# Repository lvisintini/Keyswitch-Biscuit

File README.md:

# Keyswitch-Biscuit
This is a Kicad project outlining the desing and gerbers for a Keyboard Switch Biscuits

## What is it?

This small PCB fits a single Cherry MX style mechanical keyboard switch and exposes all the connections for easy soldering.

It's designed for those of you interested in making hand-wired custom mechanical keyboards like the [Dactyl Manuform](https://github.com/abstracthat/dactyl-manuform)

There are a bunch of of these around, but this one is different in that:

- It is designed to be used with Kailh hotswap sockets (for solderless removal of keyswitches)
- It has a slot for a [SK6812 MINI-E](https://hackaday.com/2020/01/28/new-part-day-sk6812-mini-e-a-hand-solderable-neopixel-compatible-led/) downward-facing RGB surface mounted LED (you can get a bunch of them [here](https://www.ebay.co.uk/itm/174769617449)
- Allows you to solder the entire key matrix before installing it inside the case. (no need to do this in place)

This design in particular has indentations in each corner so that melted plastic can be used to hold the PCB in place, without the need of glue or screws (though you could still use those if you wanted to)

I designed this when I was preparing to make my own Dactyl Manuform keyboard.

See.. it's layout and shape not flat and it's not possible to buy/make a single board with all the terminals for the key switches you need. This is when this small PCB comes in handy.

You could hand-wire all the key switches together but it would be messy and you would be hard pressed if you wanted to use Kailh hotswap sockets or any kind of RGB features.

## Version and Gerbers
### **v1.0** (gerbers/gerbers-v1.0.zip)

First iteration of the desing.

The RBG footprint used for the SK6812 MINI-E was messed up and the connections did not match.

The board was successfully printed with JLCPCB (as 5x5 panel), the only the Rows and Cols are really usable.

Leaving this hear for the sake of archiving.

### **v1.1** (gerbers/gerbers-v1.1.zip)

This version was the first usable MVP and it was successfully used in my own Dactyl Manuform build.

Works great!

The board was successfully printed with JLCPCB though I dont remember doing much checking tolerances.

I used a 1.6 thickness with a 1oz copper layer and a LeadFree HASL-RoHS finish.

Potentially improvements:
    
 -  Solid Pads instead of THT may allow for easier wiring (though they may require better soldering skills)
 -  The traces themselves could be a bit thicker (not sure if there is enough space)#

## Bonus

mount.stl is 3D-printable part that can be used to firmly hold in place the Keyswitch-Biscuit to allow for easy soldering.
It can come in handy to get a few of these and glue them to a working surface, spaced so that there is equal distances between them.
If you are planning on hand-wiring a large matrix, it may make it easy to solder the wires and keep of a consistent length.

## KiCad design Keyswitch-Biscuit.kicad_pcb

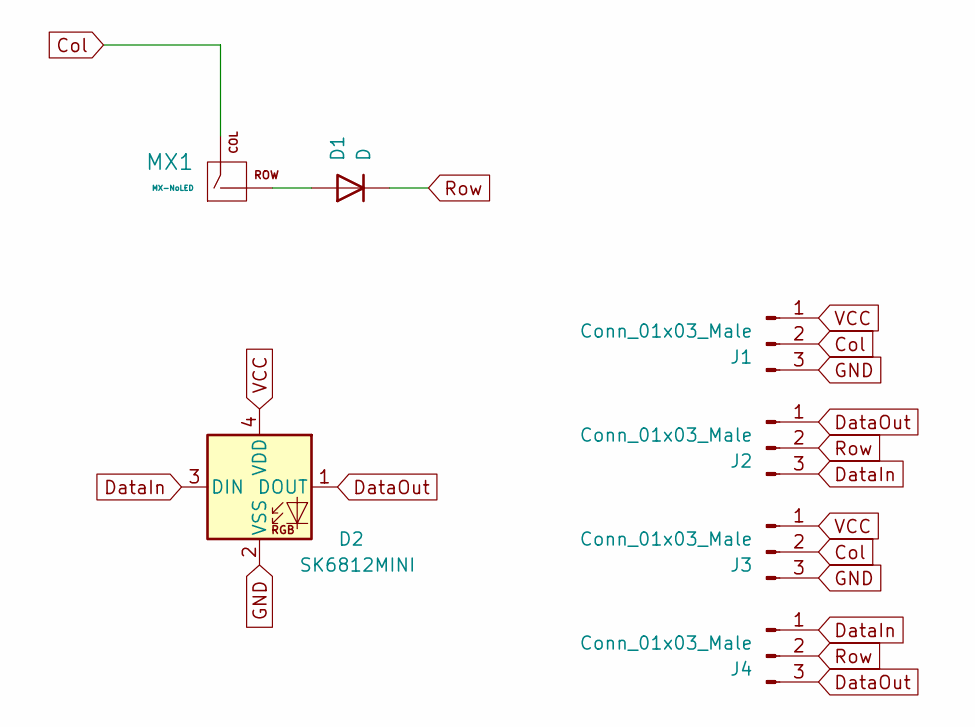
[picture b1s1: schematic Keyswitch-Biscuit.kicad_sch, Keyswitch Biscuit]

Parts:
D1: D; D_SOD-123
D2: SK6812MINI; SK6812MINI_rev
J1, J2, J3, J4: Conn_01x03_Male; SolderWire-0.1sqmm_1x03_D0.4mm_OD1mm
MX1: MX-NoLED; MXOnly-1U-Hotswap-v2

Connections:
Col: J1.2, J3.2, MX1.1 (COL)
DataIn: D2.3 (DIN), J2.3, J4.1
DataOut: D2.1 (DOUT), J2.1, J4.3
GND: D2.2 (VSS), J1.3, J3.3
unnamed: D1.2 (A), MX1.2 (ROW)
Row: D1.1 (K), J2.2, J4.2
VCC: D2.4 (VDD), J1.1, J3.1

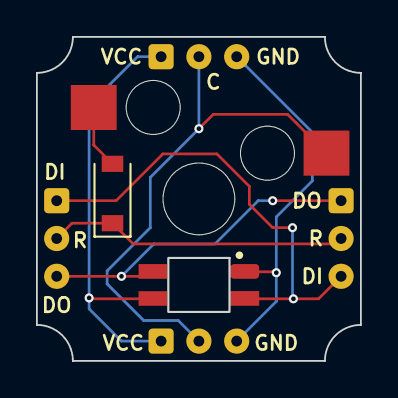
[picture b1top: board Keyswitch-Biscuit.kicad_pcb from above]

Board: 2 copper layers, 18.0 x 18.0 mm, 7 parts (1 on the bottom side), 7 nets.

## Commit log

2021-06-30 v1.0 of custom biscuit (good start)
2021-06-30 Updated RGB LED footprint to match reversed variant. Retraced All. Replaced corner holes for notches.
2022-03-12 Added mount file for easy soldering. Initial updates to KiCad 6
2022-03-12 Files auto-upgraded to KiCad 6
2023-07-08 Looked into tolerances and it turns out I should be okay making traces quite a lot smaller
